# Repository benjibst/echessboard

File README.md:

https://benjibst.github.io/pdfs/echessboard_report.pdf

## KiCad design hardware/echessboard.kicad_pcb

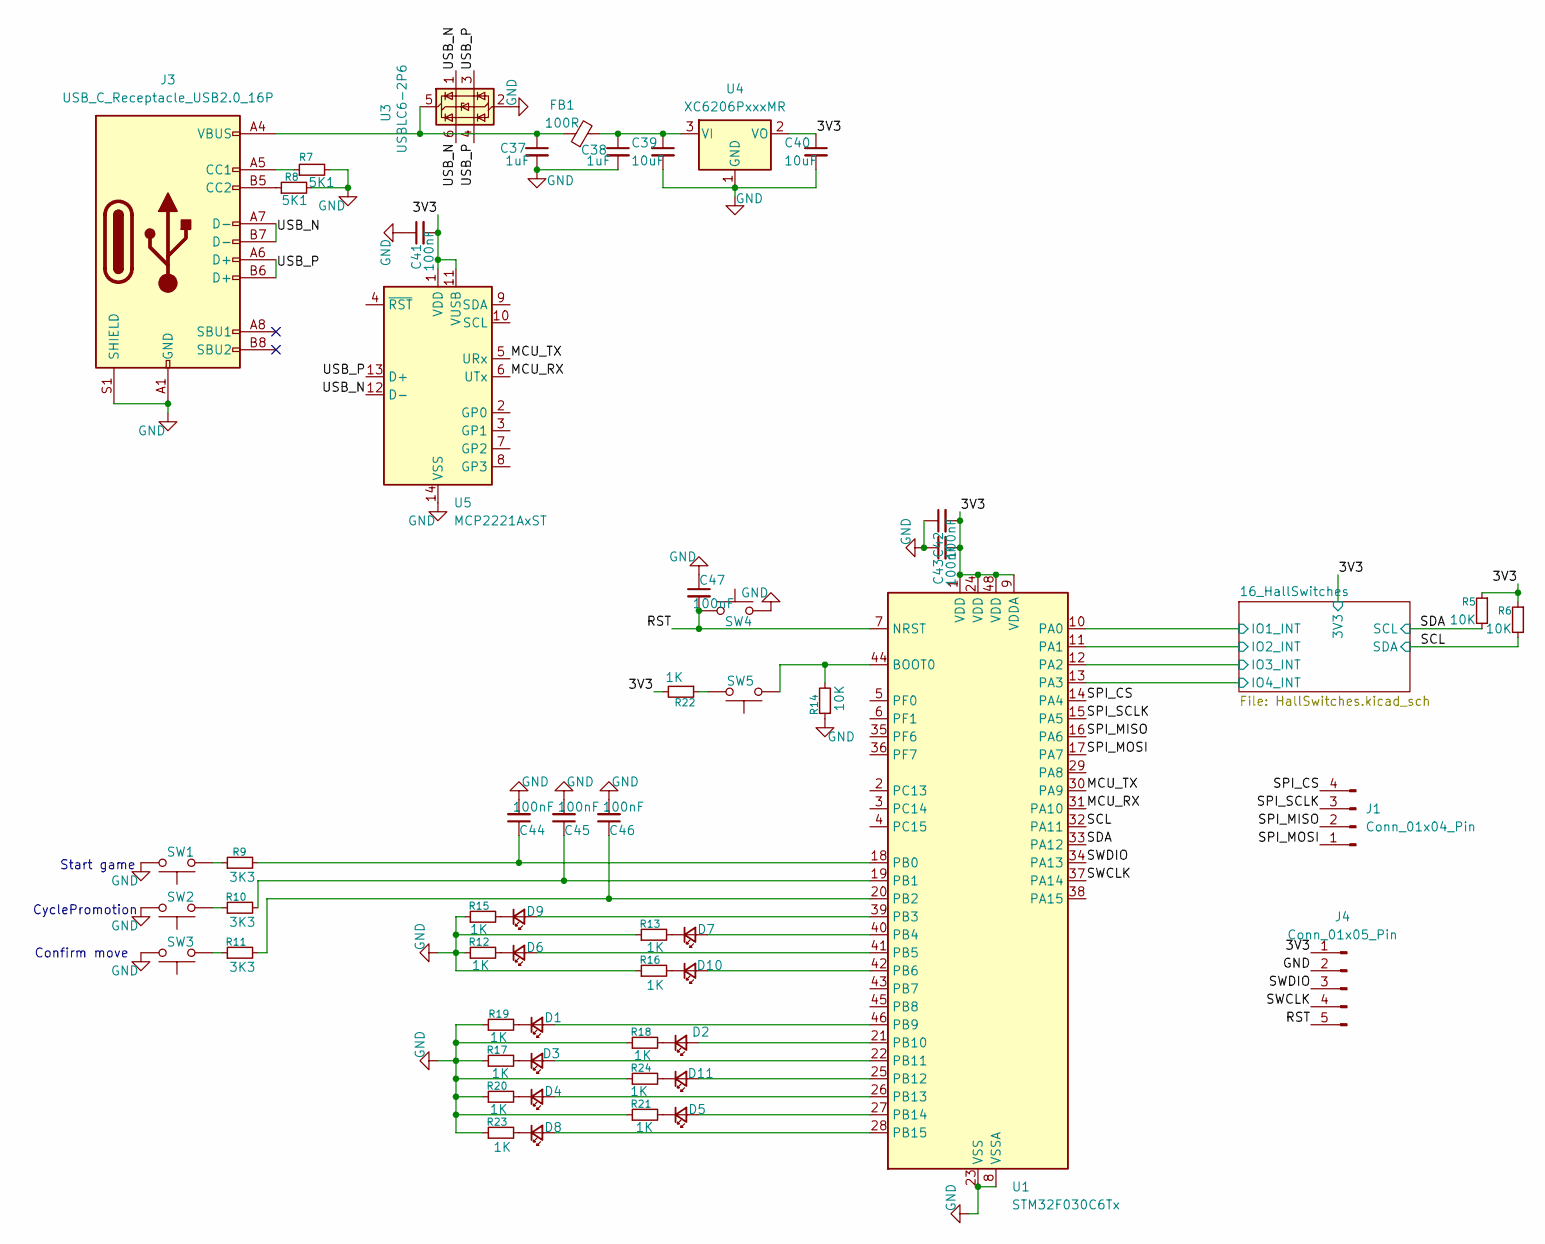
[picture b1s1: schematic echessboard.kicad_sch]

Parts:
C37, C38: 1uF; C_0805_2012Metric; LCSC C28323
C39, C40: 10uF; C_1206_3216Metric; LCSC C13585
C41, C42, C43, C44, C45, C46, C47: 100nF; C_0603_1608Metric; LCSC C14663
D1, D2, D3, D4, D5, D6, D7, D8, D9, D10, D11: LED_0603_1608Metric; LCSC C2286
FB1: 100R; L_0603_1608Metric; LCSC C1002
J1: Conn_01x04_Pin; PinHeader_1x04_P2.54mm_Vertical
J3: USB_C_Receptacle_USB2.0_16P; USB_C_Receptacle_HRO_TYPE-C-31-M-12; LCSC C165948
J4: Conn_01x05_Pin; PinHeader_1x05_P2.54mm_Vertical
R5, R6, R14: 10K; R_0603_1608Metric; LCSC C25804
R7, R8: 5K1; R_0603_1608Metric; LCSC C23186
R9, R10, R11: 3K3; R_0603_1608Metric; LCSC C22978
R12, R13, R15, R16, R17, R18, R19, R20, R21, R22, R23, R24: 1K; R_0603_1608Metric; LCSC C21190
SW1, SW2, SW3, SW4, SW5: SW_Push; SW_SPST_TL3342; LCSC C318884
U1: STM32F030C6Tx; LQFP-48_7x7mm_P0.5mm; LCSC C62514
U3: USBLC6-2P6; SOT-666; LCSC C15999
U4: XC6206PxxxMR; SOT-23-3; LCSC C5446
U5: MCP2221AxST; TSSOP-14_4.4x5mm_P0.65mm; LCSC C130462

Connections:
/3V3: C40.1, C41.2, C42.2, C43.2, J4.1, R5.1, R6.1, R22.2, U1.1 (VDD), U1.9 (VDDA), U1.24 (VDD), U1.48 (VDD), U4.2 (VO), U5.1 (VDD), U5.11 (VUSB); also elsewhere on the board
/16_HallSwitches/IO1_INT: U1.10 (PA0); also elsewhere on the board
/16_HallSwitches/IO2_INT: U1.11 (PA1); also elsewhere on the board
/16_HallSwitches/IO3_INT: U1.12 (PA2); also elsewhere on the board
/16_HallSwitches/IO4_INT: U1.13 (PA3); also elsewhere on the board
/MCU_RX: U1.31 (PA10), U5.6 (UTx)
/MCU_TX: U1.30 (PA9), U5.5 (URx)
/RST: C47.2, J4.5, SW4.1, U1.7 (NRST)
/SCL: R6.2, U1.32 (PA11); also elsewhere on the board
/SDA: R5.2, U1.33 (PA12); also elsewhere on the board
/SPI_CS: J1.4, U1.14 (PA4)
/SPI_MISO: J1.2, U1.16 (PA6)
/SPI_MOSI: J1.1, U1.17 (PA7)
/SPI_SCLK: J1.3, U1.15 (PA5)
/SWCLK: J4.4, U1.37 (PA14)
/SWDIO: J4.3, U1.34 (PA13)
/USB_N: J3.A7 (D-), J3.B7 (D-), U3.1 (I/O1), U3.6 (I/O1), U5.12 (D-)
/USB_P: J3.A6 (D+), J3.B6 (D+), U3.3 (I/O2), U3.4 (I/O2), U5.13 (D+)
GND: C37.2, C38.2, C39.2, C40.2, C41.1, C42.1, C43.1, C44.2, C45.2, C46.2, C47.1, J3.A1 (GND), J3.A12 (GND), J3.B1 (GND), J3.B12 (GND), J3.S1 (SHIELD), J4.2, R7.2, R8.2, R12.1, R13.1, R14.1, R15.1, R16.1, R17.1, R18.1, R19.1, R20.1, R21.1, R23.1, R24.1, SW1.1, SW2.1, SW3.1, SW4.2, U1.8 (VSSA), U1.23 (VSS), U1.47 (VSS), U3.2 (GND), U4.1 (GND), U5.14 (VSS); also elsewhere on the board
unnamed: D1.2 (A), U1.46 (PB9)
unnamed: D1.1 (K), R19.2
unnamed: D2.2 (A), U1.21 (PB10)
unnamed: D2.1 (K), R18.2
unnamed: D3.2 (A), U1.22 (PB11)
unnamed: D3.1 (K), R17.2
unnamed: D4.2 (A), U1.26 (PB13)
unnamed: D4.1 (K), R20.2
unnamed: D5.2 (A), U1.27 (PB14)
unnamed: D5.1 (K), R21.2
unnamed: D6.2 (A), U1.41 (PB5)
unnamed: D6.1 (K), R12.2
unnamed: D7.2 (A), U1.40 (PB4)
unnamed: D7.1 (K), R13.2
unnamed: D8.2 (A), U1.28 (PB15)
unnamed: D8.1 (K), R23.2
unnamed: D9.2 (A), U1.39 (PB3)
unnamed: D9.1 (K), R15.2
unnamed: D10.2 (A), U1.42 (PB6)
unnamed: D10.1 (K), R16.2
unnamed: D11.2 (A), U1.25 (PB12)
unnamed: D11.1 (K), R24.2
unnamed: J3.A5 (CC1), R7.1
unnamed: J3.B5 (CC2), R8.1
unnamed: R9.1, SW1.2
unnamed: R10.1, SW2.2
unnamed: R11.1, SW3.2
unnamed: R22.1, SW5.2
unnamed: R14.2, SW5.1, U1.44 (BOOT0)
unnamed: C44.1, R9.2, U1.18 (PB0)
unnamed: C45.1, R10.2, U1.19 (PB1)
unnamed: C46.1, R11.2, U1.20 (PB2)
unnamed: C37.1, FB1.1, J3.A4 (VBUS), J3.A9 (VBUS), J3.B4 (VBUS), J3.B9 (VBUS), U3.5 (VBUS)
unnamed: C38.1, C39.1, FB1.2, U4.3 (VI)

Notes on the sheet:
Confirm move
Start game
CyclePromotion

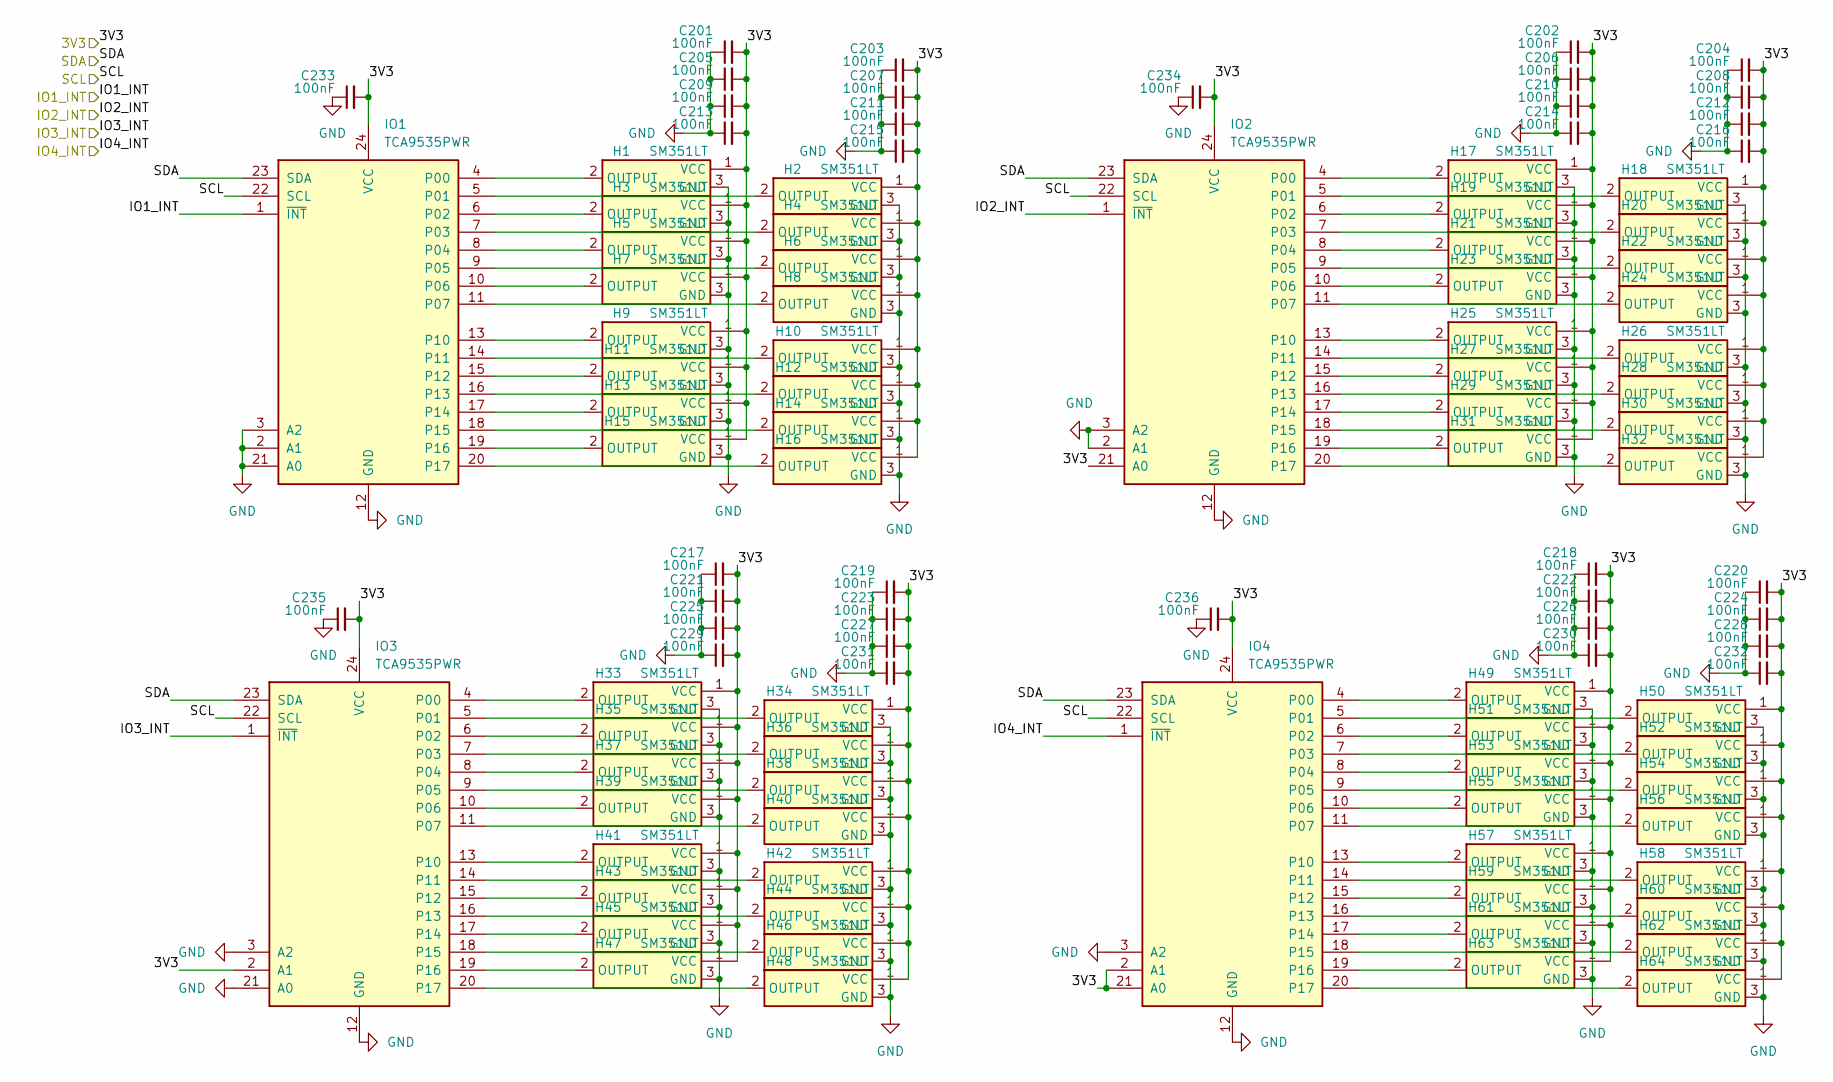
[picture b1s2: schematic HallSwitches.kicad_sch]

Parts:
C201, C202, C203, C204, C205, C206, C207, C208, C209, C210, C211, C212, C213, C214, C215, C216, C217, C218, C219, C220, C221, C222, C223, C224, C225, C226, C227, C228, C229, C230, C231, C232, C233, C234, C235, C236: 100nF; C_0603_1608Metric; LCSC C14663
H1, H2, H3, H4, H5, H6, H7, H8, H9, H10, H11, H12, H13, H14, H15, H16, H17, H18, H19, H20, H21, H22, H23, H24, H25, H26, H27, H28, H29, H30, H31, H32, H33, H34, H35, H36, H37, H38, H39, H40, H41, H42, H43, H44, H45, H46, H47, H48, H49, H50, H51, H52, H53, H54, H55, H56, H57, H58, H59, H60, H61, H62, H63, H64: SM351LT; SOT-23; LCSC C22466024
IO1, IO2, IO3, IO4: TCA9535PWR; TSSOP-24_4.4x7.8mm_P0.65mm; LCSC C22396388

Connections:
/3V3: C201.2, C202.2, C203.2, C204.2, C205.2, C206.2, C207.2, C208.2, C209.2, C210.2, C211.2, C212.2, C213.2, C214.2, C215.2, C216.2, C217.2, C218.2, C219.2, C220.2, C221.2, C222.2, C223.2, C224.2, C225.2, C226.2, C227.2, C228.2, C229.2, C230.2, C231.2, C232.2, C233.2, C234.2, C235.2, C236.2, H1.1 (VCC), H2.1 (VCC), H3.1 (VCC), H4.1 (VCC), H5.1 (VCC), H6.1 (VCC), H7.1 (VCC), H8.1 (VCC), H9.1 (VCC), H10.1 (VCC), H11.1 (VCC), H12.1 (VCC), H13.1 (VCC), H14.1 (VCC), H15.1 (VCC), H16.1 (VCC), H17.1 (VCC), H18.1 (VCC), H19.1 (VCC), H20.1 (VCC), H21.1 (VCC), H22.1 (VCC), H23.1 (VCC), H24.1 (VCC), H25.1 (VCC), H26.1 (VCC), H27.1 (VCC), H28.1 (VCC), H29.1 (VCC), H30.1 (VCC), H31.1 (VCC), H32.1 (VCC), H33.1 (VCC), H34.1 (VCC), H35.1 (VCC), H36.1 (VCC), H37.1 (VCC), H38.1 (VCC), H39.1 (VCC), H40.1 (VCC), H41.1 (VCC), H42.1 (VCC), H43.1 (VCC), H44.1 (VCC), H45.1 (VCC), H46.1 (VCC), H47.1 (VCC), H48.1 (VCC), H49.1 (VCC), H50.1 (VCC), H51.1 (VCC), H52.1 (VCC), H53.1 (VCC), H54.1 (VCC), H55.1 (VCC), H56.1 (VCC), H57.1 (VCC), H58.1 (VCC), H59.1 (VCC), H60.1 (VCC), H61.1 (VCC), H62.1 (VCC), H63.1 (VCC), H64.1 (VCC), IO1.24 (VCC), IO2.21 (A0), IO2.24 (VCC), IO3.2 (A1), IO3.24 (VCC), IO4.2 (A1), IO4.21 (A0), IO4.24 (VCC); also elsewhere on the board
/16_HallSwitches/IO1_INT: IO1.1 (~INT); also elsewhere on the board
/16_HallSwitches/IO2_INT: IO2.1 (~INT); also elsewhere on the board
/16_HallSwitches/IO3_INT: IO3.1 (~INT); also elsewhere on the board
/16_HallSwitches/IO4_INT: IO4.1 (~INT); also elsewhere on the board
/SCL: IO1.23 (SDA), IO2.23 (SDA), IO3.23 (SDA), IO4.23 (SDA); also elsewhere on the board
/SDA: IO1.22 (SCL), IO2.22 (SCL), IO3.22 (SCL), IO4.22 (SCL); also elsewhere on the board
GND: C201.1, C202.1, C203.1, C204.1, C205.1, C206.1, C207.1, C208.1, C209.1, C210.1, C211.1, C212.1, C213.1, C214.1, C215.1, C216.1, C217.1, C218.1, C219.1, C220.1, C221.1, C222.1, C223.1, C224.1, C225.1, C226.1, C227.1, C228.1, C229.1, C230.1, C231.1, C232.1, C233.1, C234.1, C235.1, C236.1, H1.3 (GND), H2.3 (GND), H3.3 (GND), H4.3 (GND), H5.3 (GND), H6.3 (GND), H7.3 (GND), H8.3 (GND), H9.3 (GND), H10.3 (GND), H11.3 (GND), H12.3 (GND), H13.3 (GND), H14.3 (GND), H15.3 (GND), H16.3 (GND), H17.3 (GND), H18.3 (GND), H19.3 (GND), H20.3 (GND), H21.3 (GND), H22.3 (GND), H23.3 (GND), H24.3 (GND), H25.3 (GND), H26.3 (GND), H27.3 (GND), H28.3 (GND), H29.3 (GND), H30.3 (GND), H31.3 (GND), H32.3 (GND), H33.3 (GND), H34.3 (GND), H35.3 (GND), H36.3 (GND), H37.3 (GND), H38.3 (GND), H39.3 (GND), H40.3 (GND), H41.3 (GND), H42.3 (GND), H43.3 (GND), H44.3 (GND), H45.3 (GND), H46.3 (GND), H47.3 (GND), H48.3 (GND), H49.3 (GND), H50.3 (GND), H51.3 (GND), H52.3 (GND), H53.3 (GND), H54.3 (GND), H55.3 (GND), H56.3 (GND), H57.3 (GND), H58.3 (GND), H59.3 (GND), H60.3 (GND), H61.3 (GND), H62.3 (GND), H63.3 (GND), H64.3 (GND), IO1.2 (A1), IO1.3 (A2), IO1.12 (GND), IO1.21 (A0), IO2.2 (A1), IO2.3 (A2), IO2.12 (GND), IO3.3 (A2), IO3.12 (GND), IO3.21 (A0), IO4.3 (A2), IO4.12 (GND); also elsewhere on the board
unnamed: H1.2 (OUTPUT), IO1.4 (P00)
unnamed: H2.2 (OUTPUT), IO1.5 (P01)
unnamed: H3.2 (OUTPUT), IO1.6 (P02)
unnamed: H4.2 (OUTPUT), IO1.7 (P03)
unnamed: H5.2 (OUTPUT), IO1.8 (P04)
unnamed: H6.2 (OUTPUT), IO1.9 (P05)
unnamed: H7.2 (OUTPUT), IO1.10 (P06)
unnamed: H8.2 (OUTPUT), IO1.11 (P07)
unnamed: H9.2 (OUTPUT), IO1.13 (P10)
unnamed: H10.2 (OUTPUT), IO1.14 (P11)
unnamed: H11.2 (OUTPUT), IO1.15 (P12)
unnamed: H12.2 (OUTPUT), IO1.16 (P13)
unnamed: H13.2 (OUTPUT), IO1.17 (P14)
unnamed: H14.2 (OUTPUT), IO1.18 (P15)
unnamed: H15.2 (OUTPUT), IO1.19 (P16)
unnamed: H16.2 (OUTPUT), IO1.20 (P17)
unnamed: H17.2 (OUTPUT), IO2.4 (P00)
unnamed: H18.2 (OUTPUT), IO2.5 (P01)
unnamed: H19.2 (OUTPUT), IO2.6 (P02)
unnamed: H20.2 (OUTPUT), IO2.7 (P03)
unnamed: H21.2 (OUTPUT), IO2.8 (P04)
unnamed: H22.2 (OUTPUT), IO2.9 (P05)
unnamed: H23.2 (OUTPUT), IO2.10 (P06)
unnamed: H24.2 (OUTPUT), IO2.11 (P07)
unnamed: H25.2 (OUTPUT), IO2.13 (P10)
unnamed: H26.2 (OUTPUT), IO2.14 (P11)
unnamed: H27.2 (OUTPUT), IO2.15 (P12)
unnamed: H28.2 (OUTPUT), IO2.16 (P13)
unnamed: H29.2 (OUTPUT), IO2.17 (P14)
unnamed: H30.2 (OUTPUT), IO2.18 (P15)
unnamed: H31.2 (OUTPUT), IO2.19 (P16)
unnamed: H32.2 (OUTPUT), IO2.20 (P17)
unnamed: H33.2 (OUTPUT), IO3.4 (P00)
unnamed: H34.2 (OUTPUT), IO3.5 (P01)
unnamed: H35.2 (OUTPUT), IO3.6 (P02)
unnamed: H36.2 (OUTPUT), IO3.7 (P03)
unnamed: H37.2 (OUTPUT), IO3.8 (P04)
unnamed: H38.2 (OUTPUT), IO3.9 (P05)
unnamed: H39.2 (OUTPUT), IO3.10 (P06)
unnamed: H40.2 (OUTPUT), IO3.11 (P07)
unnamed: H41.2 (OUTPUT), IO3.13 (P10)
unnamed: H42.2 (OUTPUT), IO3.14 (P11)
unnamed: H43.2 (OUTPUT), IO3.15 (P12)
unnamed: H44.2 (OUTPUT), IO3.16 (P13)
unnamed: H45.2 (OUTPUT), IO3.17 (P14)
unnamed: H46.2 (OUTPUT), IO3.18 (P15)
unnamed: H47.2 (OUTPUT), IO3.19 (P16)
unnamed: H48.2 (OUTPUT), IO3.20 (P17)
unnamed: H49.2 (OUTPUT), IO4.4 (P00)
unnamed: H50.2 (OUTPUT), IO4.5 (P01)
unnamed: H51.2 (OUTPUT), IO4.6 (P02)
unnamed: H52.2 (OUTPUT), IO4.7 (P03)
unnamed: H53.2 (OUTPUT), IO4.8 (P04)
unnamed: H54.2 (OUTPUT), IO4.9 (P05)
unnamed: H55.2 (OUTPUT), IO4.10 (P06)
unnamed: H56.2 (OUTPUT), IO4.11 (P07)
unnamed: H57.2 (OUTPUT), IO4.13 (P10)
unnamed: H58.2 (OUTPUT), IO4.14 (P11)
unnamed: H59.2 (OUTPUT), IO4.15 (P12)
unnamed: H60.2 (OUTPUT), IO4.16 (P13)
unnamed: H61.2 (OUTPUT), IO4.17 (P14)
unnamed: H62.2 (OUTPUT), IO4.18 (P15)
unnamed: H63.2 (OUTPUT), IO4.19 (P16)
unnamed: H64.2 (OUTPUT), IO4.20 (P17)

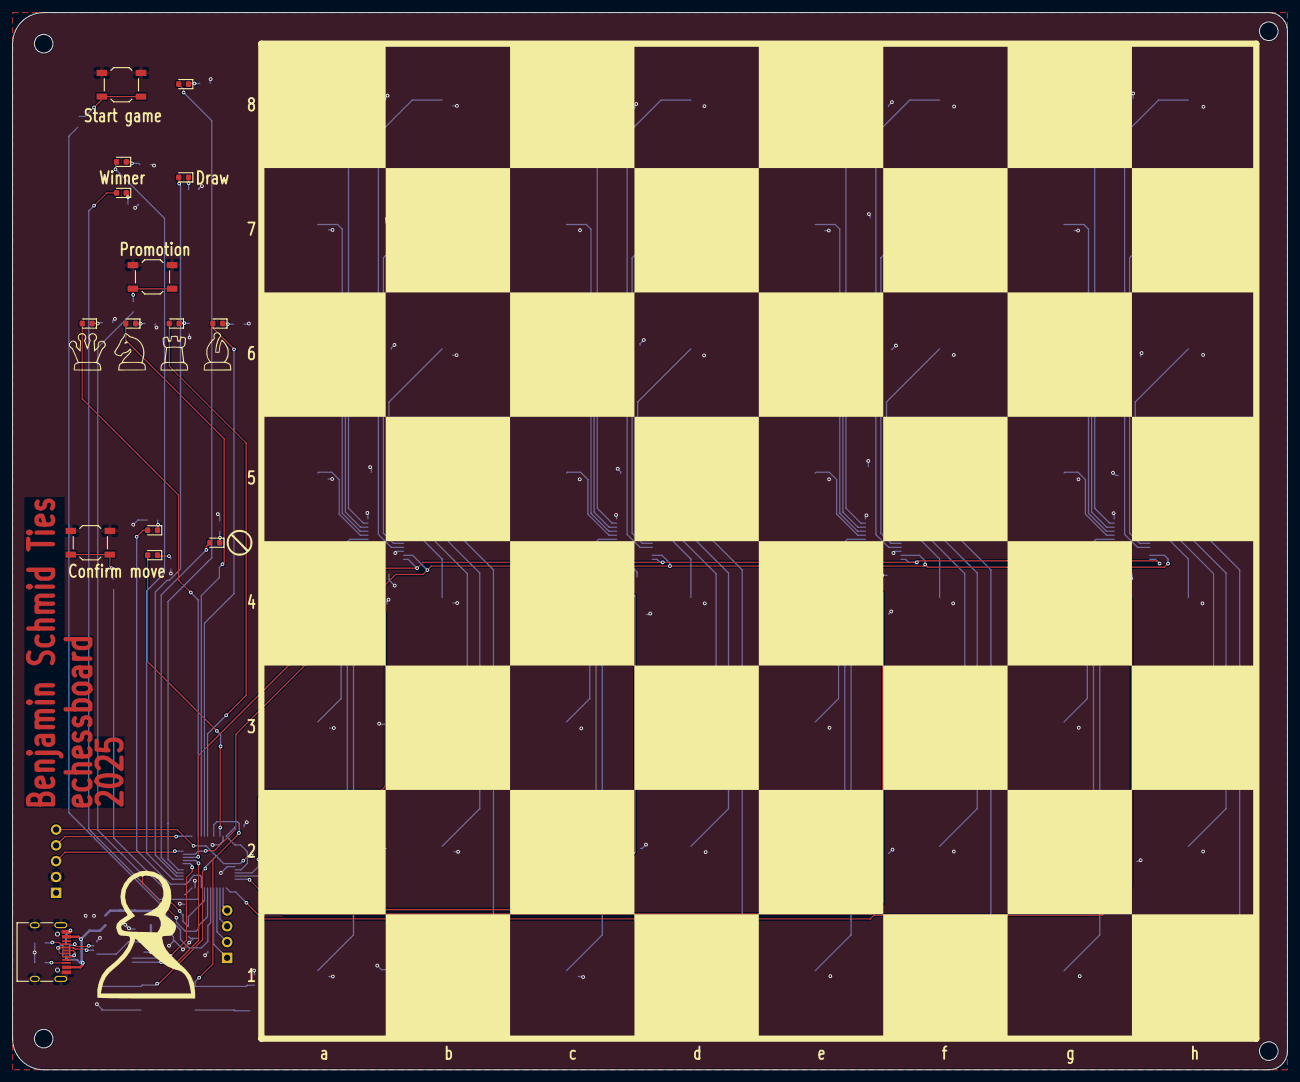
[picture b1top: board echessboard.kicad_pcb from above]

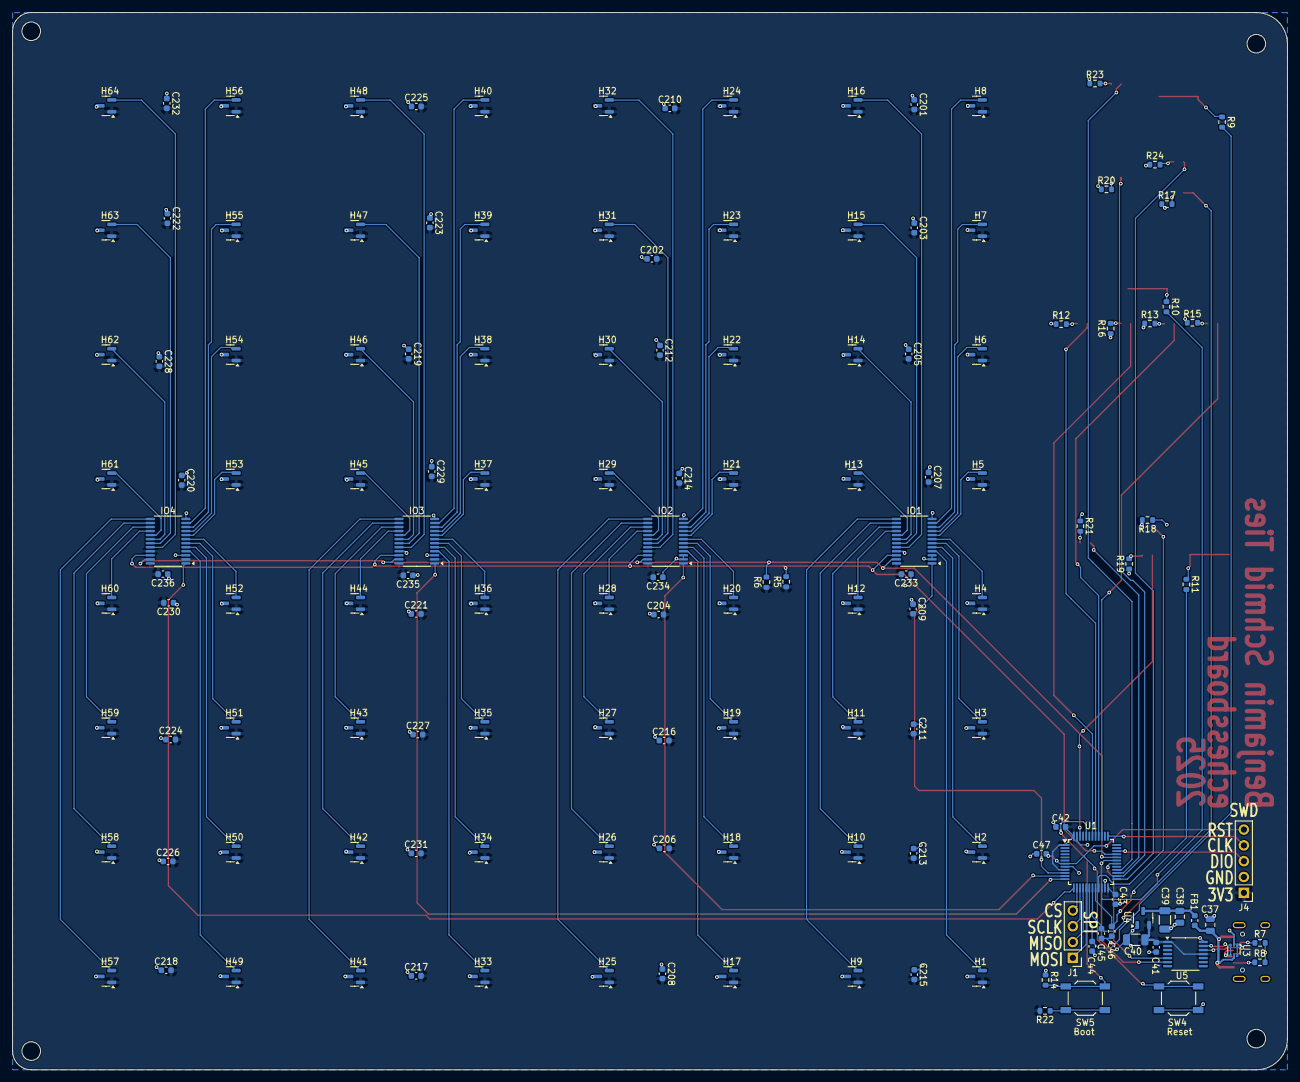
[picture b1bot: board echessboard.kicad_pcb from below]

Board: 2 copper layers, 205.0 x 170.0 mm, 159 parts (144 on the bottom side), 117 nets.

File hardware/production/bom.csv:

Designator,Footprint,Quantity,Value,LCSC Part #
"C201, C202, C203, C204, C205, C206, C207, C208, C209, C210, C211, C212, C213, C214, C215, C216, C217, C218, C219, C220, C221, C222, C223, C224, C225, C226, C227, C228, C229, C230, C231, C232, C233, C234, C235, C236, C41, C42, C43, C44, C45, C46, C47",0603,43,100nF,C14663
"C37, C38",0805,2,1uF,C28323
"C39, C40",1206,2,10uF,C13585
"D1, D10, D11, D2, D3, D4, D5, D6, D7, D8, D9",0603,11,~,C2286
FB1,0603,1,100R,C1002
"H1, H10, H11, H12, H13, H14, H15, H16, H17, H18, H19, H2, H20, H21, H22, H23, H24, H25, H26, H27, H28, H29, H3, H30, H31, H32, H33, H34, H35, H36, H37, H38, H39, H4, H40, H41, H42, H43, H44, H45, H46, H47, H48, H49, H5, H50, H51, H52, H53, H54, H55, H56, H57, H58, H59, H6, H60, H61, H62, H63, H64, H7, H8, H9",SOT-23,64,SM351LT,C22466024
"IO1, IO2, IO3, IO4",TSSOP-24_4.4x7.8mm_P0.65mm,4,TCA9535PWR,C22396388
J3,USB_C_Receptacle_HRO_TYPE-C-31-M-12,1,USB_C_Receptacle_USB2.0_16P,C165948
"R10, R11, R9",0603,3,3K3,C22978
"R12, R13, R15, R16, R17, R18, R19, R20, R21, R22, R23, R24",0603,12,1K,C21190
"R14, R5, R6",0603,3,10K,C25804
"R7, R8",0603,2,5K1,C23186
"SW1, SW2, SW3, SW4, SW5",SW_SPST_TL3342,5,SW_Push,C318884 
U1,LQFP-48_7x7mm_P0.5mm,1,STM32F030C6Tx,C62514
U3,SOT-666,1,USBLC6-2P6,C15999
U4,SOT-23-3,1,XC6206PxxxMR,C5446
U5,TSSOP-14_4.4x5mm_P0.65mm,1,MCP2221AxST,C130462

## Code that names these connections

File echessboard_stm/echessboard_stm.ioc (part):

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Mcu.Name=STM32F030C6Tx
Mcu.Package=LQFP48
Mcu.UserName=STM32F030C6Tx
PA0.GPIOParameters=GPIO_PuPd
PA0.GPIO_PuPd=GPIO_PULLUP
PA0.Signal=GPIO_Input
PA1.GPIOParameters=GPIO_PuPd
PA1.GPIO_PuPd=GPIO_PULLUP
PA1.Signal=GPIO_Input
PA10.Mode=Asynchronous
PA10.Signal=USART1_RX
PA11.GPIOParameters=GPIO_PuPd,GPIO_Label,GPIO_ModeDefaultOutputPP
PA11.GPIO_Label=SW_I2C_SDA
PA11.GPIO_ModeDefaultOutputPP=GPIO_MODE_OUTPUT_OD
PA11.GPIO_PuPd=GPIO_PULLUP
PA11.Signal=GPIO_Output
PA12.GPIOParameters=GPIO_PuPd,GPIO_Label,GPIO_ModeDefaultOutputPP
PA12.GPIO_Label=SW_I2C_SCL
PA12.GPIO_ModeDefaultOutputPP=GPIO_MODE_OUTPUT_OD
PA12.GPIO_PuPd=GPIO_PULLUP
PA12.Signal=GPIO_Output
PA13.Mode=Serial_Wire
PA13.Signal=SYS_SWDIO
PA14.Mode=Serial_Wire
PA14.Signal=SYS_SWCLK
PA2.GPIOParameters=GPIO_PuPd
PA2.GPIO_PuPd=GPIO_PULLUP
PA2.Signal=GPIO_Input
PA3.GPIOParameters=GPIO_PuPd
PA3.GPIO_PuPd=GPIO_PULLUP
PA3.Signal=GPIO_Input
PA4.Mode=NSS_Signal_Hard_Output
PA4.Signal=SPI1_NSS
PA5.Mode=Full_Duplex_Master
PA5.Signal=SPI1_SCK
PA6.Mode=Full_Duplex_Master
PA6.Signal=SPI1_MISO
PA7.Mode=Full_Duplex_Master
PA7.Signal=SPI1_MOSI
PA9.Mode=Asynchronous
PA9.Signal=USART1_TX
PB0.GPIOParameters=GPIO_PuPd,GPIO_ModeDefaultEXTI
PB0.GPIO_ModeDefaultEXTI=GPIO_MODE_IT_FALLING
PB0.GPIO_PuPd=GPIO_PULLUP
PB0.Signal=GPXTI0
PB1.GPIOParameters=GPIO_PuPd,GPIO_ModeDefaultEXTI
PB1.GPIO_ModeDefaultEXTI=GPIO_MODE_IT_FALLING
PB1.GPIO_PuPd=GPIO_PULLUP
PB1.Signal=GPXTI1
PB10.Signal=GPIO_Output
PB11.Signal=GPIO_Output
PB12.Signal=GPIO_Output
PB13.Signal=GPIO_Output
PB14.Signal=GPIO_Output
PB15.Signal=GPIO_Output
PB2.GPIOParameters=GPIO_PuPd,GPIO_ModeDefaultEXTI
PB2.GPIO_ModeDefaultEXTI=GPIO_MODE_IT_FALLING
PB2.GPIO_PuPd=GPIO_PULLUP
PB2.Signal=GPXTI2
PB3.Signal=GPIO_Output
PB4.Signal=GPIO_Output
PB5.Signal=GPIO_Output
PB6.Signal=GPIO_Output
PB9.Signal=GPIO_Output
RCC.SYSCLKFreq_VALUE=48000000
RCC.SYSCLKSource=RCC_SYSCLKSOURCE_PLLCLK
board=custom

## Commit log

2025-05-12 initial push
2025-05-12 sync
2025-05-13 footprints
2025-05-15 lcsc part numbers
2025-05-16 finalize
2025-05-16 production ordered
2025-05-17 project structure
2025-05-17 add submodule riscv
2025-05-17 gitignore
2025-05-19 update submodule
2025-05-20 add low res chess piece images for rendering in VGA
2025-05-25 remove riscv submodule and add vivado project
2025-05-27 fix i2c pins
2025-05-27 read working
2025-05-29 change to nexys
2025-06-01 implement chess game state
2025-06-01 data path and vga image generator and testbench
2025-06-01 add files to vivado
2025-06-02 fix code for simulation
2025-06-02 cache to gitignore
2025-06-03 asdasdads
2025-06-04 compare chess positions
2025-06-06 riscv test program and script to generate hexdump for vivado
2025-06-07 create hex dump with start address 0
2025-06-08 immediate extract unit fixed and tested
2025-06-08 test alu
2025-06-09 remove variable initializations
2025-06-09 fixed program counter (failed after removing default values)
2025-06-09 remove useless logic
2025-06-12 full read working
2025-06-12 work on timings
2025-06-13 save
2025-06-13 fix jump
2025-06-14 chess board renderer and convert images to binary format with 2 bits per pixel
2025-06-14 upgrade vivado
2025-06-15 alu test assembly
2025-06-19 test immediate assembly and fix vhdl bug
2025-06-19 alessia code
2025-06-19 allesia change
2025-06-19 testmerge
2025-06-19 hard work
2025-07-09 Working SPI and validators to simulate
2025-07-09 Aggiunta validator e SPI funzionante
2025-07-10 finish testing all rv32i instructions
2025-07-10 chess renderer
2025-07-10 vivado
2025-07-11 fill framebuffer with 12px lines
2025-07-11 image of chess piece array
2025-07-11 Alessia update
2025-07-11 update of Top and Spi slave
2025-07-11 CHESS RENDERER WORKING VGA
2025-07-11 pawn validator and relative modifications
2025-07-11 VGA WORKING FR NOW
2025-07-12 VGA WORKING WITHOUT ARTIFACTS
2025-07-12 Working testbench Alessia
2025-07-12 chessboard program stm32
2025-07-12 make renderer able to display empty fields
2025-07-12 add riscv (vga still working)
2025-07-12 fix chessboard renderer C
2025-07-12 spi update
2025-07-12 riscv outputs something resembling a chessboard (remotely)
2025-07-13 riscv render chess initial position
2025-07-13 update of memory address
2025-07-13 spi communication working
2025-07-13 CHESS WORKING CORRECTLY
2025-10-05 Add link to eChessboard report in README
2026-04-02 backup
